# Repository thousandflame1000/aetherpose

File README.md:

# Aetherpose

## Windows：下載、解壓、雙擊啟動

一般使用者請到 [GitHub Releases](https://github.com/thousandflame1000/aetherpose/releases)
下載 `AetherPose-…-windows-x64.zip`，完整解壓後雙擊 **AetherPose.exe**。
不需另裝 Python、Rust 或 SMPL。進入網頁後按「開啟影像骨架」即可使用單鏡頭追蹤。

基本模式使用程式建構的通用人體；IMU 可選配，SMPL 與 GlobalPose 為另行安裝的進階功能。
攝影機不會自動開啟；關閉啟動器會停止本次啟動的服務。
詳細步驟、版本限制與建置方式見 [Windows 快速開始](docs/WINDOWS_QUICKSTART.md)。

母關節融合 v2 已加入影像／IMU 一致性與扭轉歧義保護；量測結果及剩餘限制見 [修正與驗證](docs/parent-fusion-v2.md)。

下方為原始碼／進階功能說明。

使用單鏡頭辨識全身骨架，可搭配 0 顆或多顆 IMU 追蹤器（Arduino Nano 33 BLE）。影像與已校正 IMU 在骨架旋轉空間融合；雙前臂、雙小腿、頭與骨盆六個位置齊備時，自動使用 GlobalPose 的姿態與位移先驗。瀏覽器顯示 SMPL 人體並提供小遊戲與 Combat 對打。

**新版操作與限制：[單鏡頭＋可變數量 IMU](docs/hybrid-runtime.md)。** 舊版 TransPose 程式保留供回歸參考，不再是預設推論來源。

```
IMU 追蹤器 ──BLE──> 後端 aetherpose.exe ──ws :9009──> 網頁控制面板（追蹤器、校正、設定）
                         │
                         └──ws :9009──> frontend/mesh_bridge.py ──ws :9010──> 3D 人體、小遊戲、Combat
                                         (影像／IMU 融合＋GlobalPose)
網頁伺服器：http://127.0.0.1:18080/
```

## 開始使用

本次工作範圍為軟體成熟化，硬體穿戴不列為完成條件。不用 IMU 的環境檢查、模擬展示、驗收與交付步驟見 [軟體展示與驗收](docs/software-delivery.md)。軟體模擬結果保留其來源，不能宣稱真人動作精度。

專案圖文總覽見 [專案整理頁](docs/project-overview.html)。`config.json` 是執行時的本機設定，不納入 Git；首次啟動會建立預設值，也可先複製 `config.example.json` 為 `config.json` 再調整。

```powershell
cd aetherpose
.\setup.ps1      # 安裝主程式套件與編譯後端
.\tools\setup_hybrid.ps1 # 安裝影像模型與隔離的 GlobalPose 環境
.\run.ps1        # 啟動後端、推論與網頁，開啟瀏覽器（已在執行的服務會沿用）
.\run.ps1 -Restart  # 更新程式後：關掉舊服務，後端程式碼較新時重新編譯，再啟動
.\stop.ps1       # 關閉
```

SMPL 模型為選用：未安裝時使用通用人體，已授權模型可在 `external_paths.json` 設定。影像模型與 GlobalPose 由 `tools/setup_hybrid.ps1` 安裝到不進 Git 的 `external/`；只安裝基本影像時可加 `-SkipGlobalPose`。用 `python frontend\external_paths.py` 檢查檔案；加 `--legacy` 可檢查舊 TransPose 資料。完整步驟見 [Hybrid 操作說明](docs/hybrid-runtime.md)。

## 連接埠

18080、9009、9010 只在本機（127.0.0.1）監聽，WebSocket 也只接受本機頁面。9003 與 9002 在所有網路介面上接收 UDP，區域網路上的 Wi-Fi 追蹤器與 Quest 才連得到；同一個網路上的其他裝置也能送資料進來，在不信任的網路上請用 Windows 防火牆擋掉這兩個埠。

| 埠 | 用途 |
|---|---|
| 18080 | 網頁與本機工具 API（`webui/server.py`） |
| 9009 | 後端 WebSocket：追蹤器狀態、設定、指令 |
| 9010 | 推論服務 WebSocket：關節位置與旋轉（頁面據此算出 SMPL 人體網格） |
| 9000（送出） | OSC 骨架輸出，依 VRChat 規格送追蹤器 1–8（髖、胸、雙腳、雙膝、雙肘）與 head；預設 127.0.0.1:9000（VRChat 的 OSC 接收埠），可在「進階 › 系統」分頁修改 |
| 9003（UDP 接收） | Wi-Fi 追蹤器的 UDP 封包；設定在 `config.json` 的 `udp_input_port`，與 OSC 輸出分開 |
| 9002（UDP 接收） | Quest 頭顯與手把的姿態橋接；超過 0.5 秒沒有新資料就不使用，「進階 › 骨架」分頁顯示是否連線 |

## 專案結構

| 位置 | 內容 |
|---|---|
| `src/` | Rust 後端：BLE 接收、姿態融合、IK、OSC 輸出、錄製、WebSocket（埠 9009）。設定存在 `config.json` |
| `src/skeleton/tracker_firmware/` | 追蹤器韌體（x-io Fusion AHRS） |
| `frontend/` | `mesh_bridge.py` 推論服務（埠 9010）、`hybrid_runner.py`、`hybrid_fusion.py`、`vision_pose.py`、`globalpose_worker.py`、`smpl_fk.py`、`external_paths.py`、`body_calibration.py` |
| `webui/` | 瀏覽器介面：主控面板、共用 3D 場景與訓練場（`environment.js`）、小遊戲、Combat、場景物件與道具庫、磁力計校正；`server.py` 頁面伺服器（含本機工具 API）、`run.ps1`／`stop.ps1` |
| `tools/` | `calibrate_tracker.py` 磁力計校正與燒錄、`make_scene_props.py` 產生場景庫的訓練道具、`simulate_trackers.py` 沒有硬體時用 UDP 模擬追蹤器、`imu_axes.py` 不經後端直接用 BLE 檢視單顆 IMU（主介面「進階 › 監控」分頁的「三軸 ↗」開的是同一個頁面） |
| `recordings/` | 「進階 › 系統」分頁錄製的骨架 CSV（不進 git） |
| `logs/` | 後端、推論服務、網頁伺服器的 log 與 BLE 連線紀錄（`run.ps1` 建立，不進 git） |
| `tests/` | 軟體測試；`tests\run_software_checks.ps1` 全部執行，加 `-Live` 會啟動服務測實際流程 |

## 文件

畢設成熟化的核心範圍、分階段工作與實測通過條件見 [畢設執行計畫](docs/graduation-plan.md)。尚未完成的實體測試不得以模擬結果代替。

目前是否達到交付程度與剩餘證據，見 [畢設程度評估](docs/graduation-readiness.md)。真人正／負例的標註及分析流程見 [深蹲試次分析](docs/action-evaluation.md)。

實測前請依 [實驗記錄說明](docs/experiments.md) 保存版本、輸入來源與逐顆追蹤器紀錄。

推論更新偏慢或動作輸入被略過時，依 [效能診斷](docs/performance.md) 保存分段負載與積壓計數。

正式報告的文字工作來源為 [成果報告審閱草稿](docs/thesis-source.md)。它依現行架構與證據重整；實體實驗、作者資料及 Word 排版仍待完成，上層舊計畫書與前三章檔案保留為歷史版本。

提供老師或接手者的原始碼快照，依 [提交包說明](docs/submission.md) 建立與驗證；個人設定、模型及實驗紀錄不會自動納入。

| 文件 | 內容 |
|---|---|
| [HANDOFF.md](HANDOFF.md) | 從零開始：韌體、環境、外部檔案、啟動、磁力計校正、常見問題 |
| [webui/README.md](webui/README.md) | 網頁介面、小遊戲規則、Combat、場景物件、回歸測試 |
| [EXTERNAL_DEPENDENCIES.md](EXTERNAL_DEPENDENCIES.md) | 外部方法、資料與授權 |
| [tools/IMU_AXES_README.md](tools/IMU_AXES_README.md) | 韌體座標軸與單顆 IMU 測試 |
| [docs/acceptance-status.md](docs/acceptance-status.md) | 軟體驗收紀錄 |

## 虛擬 IMU 與遮擋模擬

參見 [互動合成實驗](tools/hybrid_simulation/README.md)：已知 3D 動作、虛擬 IMU、真實 RGB 辨識、遮擋與誤差比較。

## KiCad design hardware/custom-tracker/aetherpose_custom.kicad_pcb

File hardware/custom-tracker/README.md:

# Aetherpose 自製追蹤器 v0.1

2026-10-18。使用者已授權由設計端選型及抓預算，先以 **6 顆**樣品規劃。這是取代 Nano 33 BLE 的新電路，板上整合 MCU／BLE、九軸感測、充電、穩壓與電量量測。

**工程審閱草稿，尚未完成 KiCad 開檔／ERC／DRC、實際焊接、韌體移植及穿戴驗證。不可直接當作可下單的完成品。** `verification.json` 只記錄獨立幾何與連通性檢查，不是 KiCad 認證。未輸出 Gerber，避免未經審核資料被誤送製。

## 選定的第一版

| 功能 | 元件／設計 | 理由與限制 |
|---|---|---|
| MCU、BLE | Espressif ESP32-C3-MINI-1-H4X | 使用原廠 RF 模組，省去裸晶天線調校；取消 Arduino 開發板。首版僅用 BLE，不啟動 Wi-Fi；仍需實測耗電及六顆同連 |
| 加速度、陀螺儀 | Bosch BMI270 | 六軸，移植感測器驅動與 Fusion，不使用 LSM9DS1 的修正倍率 |
| 磁力計 | QST QMC5883P | 保留三軸磁場輸入；採 3×3 mm LGA，避免首版增加更小 WLCSP 的組裝難度。不是 QMC5883L，驅動不可混用 |
| 充電與電源路徑 | TI BQ24075RGTR | 板載充電與負載分流；100 mA USB 輸入限制，約 100 mA 充電設定 |
| 3.3 V | TI TLV75533PDBVR | 500 mA LDO；無升壓電感。低電量可用容量會受 dropout 限制，續航待量測 |
| 電池 | 受保護 1S、4.2 V 滿充、約 250 mAh | 電池須允許至少 110 mA 充電並有 10kΩ 103AT-2 曲線 NTC，或將等效外部 NTC 貼附於電池；不可用 4.35 V 化學體系代換 |
| 充電口 | USB-C，兩個 5.1kΩ CC 下拉 | 僅作 5 V 充電，資料腳未接，沒有 PD／快充 |
| 燒錄 | 六個 UART pogo 焊盤 | 六顆共用 3.3 V USB-UART／治具；沒有每板 USB-UART IC |
| 電源開關 | C&K JS202011CQN DPDT | 同步切換 LDO EN 與電池分壓來源，關機不從 A0 注入電流 |

板框 **45 × 48 mm、雙層、暫定 1.6 mm**；天線向上超出板框約 5.3 mm，因此外殼內部長度至少還要包含突出天線與機構間隙。無穿戴固定孔，採絕緣外殼卡槽固定。此版是功能打樣尺寸，尚未做最小化。

## 開啟與檔案

- `aetherpose_custom.kicad_pro`：最小專案設定，預設線寬 0.2 mm、間距 0.15 mm；需在實際 KiCad 載入時核對規則與板廠能力。
- `aetherpose_custom.kicad_sch`：KiCad 8 原生原理圖，符號內嵌，不依賴外部符號庫。符號採逐腳方塊表達，各接點有網名或 no-connect；所有腳位目前是 passive ERC 類型，所以 ERC 不會替你檢查電源輸出衝突。
- `aetherpose_custom.kicad_pcb`：新板 PCB，精確佈線狀態以 `verification.json` 與板內連線檢視為準；不是先前的 Nano 底板。
- `pcb-preview.svg`／`pcb-preview.png`：從實際路由資料產生的工程預覽，紅色上層、藍色下層。
- `schematic-preview.svg`／`schematic-preview.png`：同一腳位模型的原理圖預覽；不是 KiCad 實際 render，仍須用 KiCad 開檔複核。
- `bom.csv`：44 個板上位置的用量、料號與成本欄。前三個主要 IC 是參考單價，其餘多數為設計預留價，**不是完整已報價的採購單**。
- `pin-netlist.csv`：逐腳網表；`design.json` 是原理圖、PCB 與網表共用來源。
- `COST.md`：成本拆分與小量預算，電池／外殼不混在電子料單價內。
- `FIRMWARE.md`：GPIO、驅動、ADC、BLE 與軸向移植要求；尚未交付可燒錄的自製板韌體。
- `Aetherpose.pretty/`、`fp-lib-table`：隨附 KiCad／Espressif 上游封裝；來源見 `sources/upstream-manifest.json`。

上層 `../bom.csv`、`../aetherpose_carrier.kicad_pcb` 是停用的 Nano 插座底板，請勿採購或混用。

## 電源與充電設計

USB VBUS → BQ24075 IN；BAT → 電池；OUT → VSYS → TLV75533 → 3V3。BQ 的電源路徑可將負載電流與充電分開，避免用一般充電 IC 直接帶負載而影響終止判斷。

第一版 EN1、EN2 固定接地，採 **USB100 模式**。ILIM 以 3.24kΩ 接地，但不使用外部 ILIM 模式，不能按此阻值宣稱輸入 500 mA。ISET 8.87kΩ，按 890 AΩ 典型係數計約 100 mA，元件誤差下可接近 110 mA；輸入限制、負載及溫度可能使實際充電更低。

TMR 懸空保留原廠約 5 小時安全計時；250 mAh 為此設定的初版容量目標。若換成 500 mAh 或更大電池，需重新評估計時設定，不可只替換電池。NTC 開路時應停止充電；首件需用加熱／冷卻與開路測試驗證。無 NTC 的二線電池不可直接插上三線接頭後宣稱已完成溫度監測。

BQ24075 在足夠高的輸入下可將 OUT 調至 5.5 V；本板只允許 **5 V USB（設計輸入上限 5.25 V）**，不能把其 6.6 V 工作額定當作本板輸入額定，TLV75533 的建議輸入上限為 5.5 V。沒有 PD 協商，不可接入自行改線的高壓來源。首版未加入獨立連接器 ESD／浪湧保護元件，需在硬體審閱決定量產保護規格。

SW1：2 是 LDO_EN 公共端，5 是 BAT_SENSE 公共端。2–3／5–6 接通為 ON；2–1／5–4 接通為 OFF。OFF 將 EN 與電池分壓來源接地；充電 IC 仍可為電池充電。開關不是電池總隔離，長期收納仍需拔電池。

R7／R8 是 100kΩ／100kΩ；4.2 V 電池時 BAT_ADC 約 2.1 V。C6 100nF 配合 50kΩ 等效來源，時間常數約 5 ms。ESP32 ADC 需以校準 API 讀電壓，不能使用 Nano 的 `3.3 / 4095` 常數。

## 接頭、燒錄與組裝

J2：**1=BAT+、2=電池 NTC、3=GND**。這是自訂三芯定義，不代表與任意市售三線電池相容；核對極性與 NTC 後才做線束。

TP1=GND、TP2=3V3 參考電壓（僅量測，不注入電源）、TP3=ESP RX、TP4=ESP TX、TP5=BOOT/GPIO9、TP6=CHIP_EN。USB-UART TX 接 TP3、RX 接 TP4，共地；治具先拉 BOOT 低，再以 EN 低→高重設，之後釋放 BOOT 進行 ROM UART 燒錄。正常啟動 BOOT 由 10kΩ 上拉。治具必須使用 3.3 V 邏輯，關機時拔除或三態 UART 訊號。

QMC5883P 需回焊，不以手焊驗證細間距底部焊盤。保留封裝方向與 1 腳標記；現有腳位圖已對照各 IC 資料表，但仍需獨立覆核 **land pattern**。通用 Bosch LGA／QFN 封裝的焊墊、熱焊盤與錫膏設計也須與實際供貨封裝確認，不能只看封裝名稱相似。

天線在板邊外，外殼、電池、線束及金屬不得包住它。磁力計中心設走線／覆銅保留區，量產需按 QST 佈局規則進一步檢查周圍材料與電流迴路。充電器、電池、線束固定後重新做磁力計校正。尚未宣稱與 Nano 同等精度、續航或穩定度。

## 驗證狀態與下一道檢查

已做：資料表腳位與電源設定查閱、以共同網表產生原理圖與 PCB、FreeRouting 單執行緒佈線，以及獨立 named-net 連通性／保守焊墊間距／板邊／保留區檢查（結果以 `verification.json` 為準）。交付草稿關閉了較耗時的 post-route 最佳化；後續以 KiCad 手動調整供電與回流為優先。

本版獨立檢查結果：**PASS，28 個網路、588 段走線、38 個過孔，保守銅間距最小約 0.1507 mm**。這些數字不代表 KiCad DRC 或硬體功能已通過。

仍需：KiCad 實際載入與 ERC／DRC、封裝及機構 1:1 對照、接頭及充電溫度審閱、回焊規格、電源完整性與接地回流審閱。首版走線以 0.2 mm 為主；供電／地線、熱焊盤與接地平面須在 KiCad 內按電流及 RF 要求優化，不能把自動佈線的連通性當成電氣性能驗收。

首件以限流供電檢查 3V3、關機分壓、低電量／USB 插拔、充電電流、NTC、燒錄、感測器 ID 與軸向；移植韌體後才測六顆 BLE、100Hz 目標、延遲及穿戴精度。所有通過項目均應留下實測記錄。

## 重建

`python build_design.py` 會重建原理圖與 **未佈線 placement PCB**，覆蓋先前 PCB；之後必須重新路由或在 KiCad 手動走線。FreeRouting 1.9 使用單執行緒 `-mt 1`；不要使用有已知間距問題的多執行緒最佳化。

目前環境可用 Java 21。`java -jar sources/freerouting-1.9.0.jar -de aetherpose_custom.dsn -do aetherpose_custom.ses -mp 20 -mt 1` 完成後，執行 `python import_and_check.py` 匯入並檢查。此程式需 Shapely。預覽 PNG 需 PyMuPDF，由 SVG 轉換。

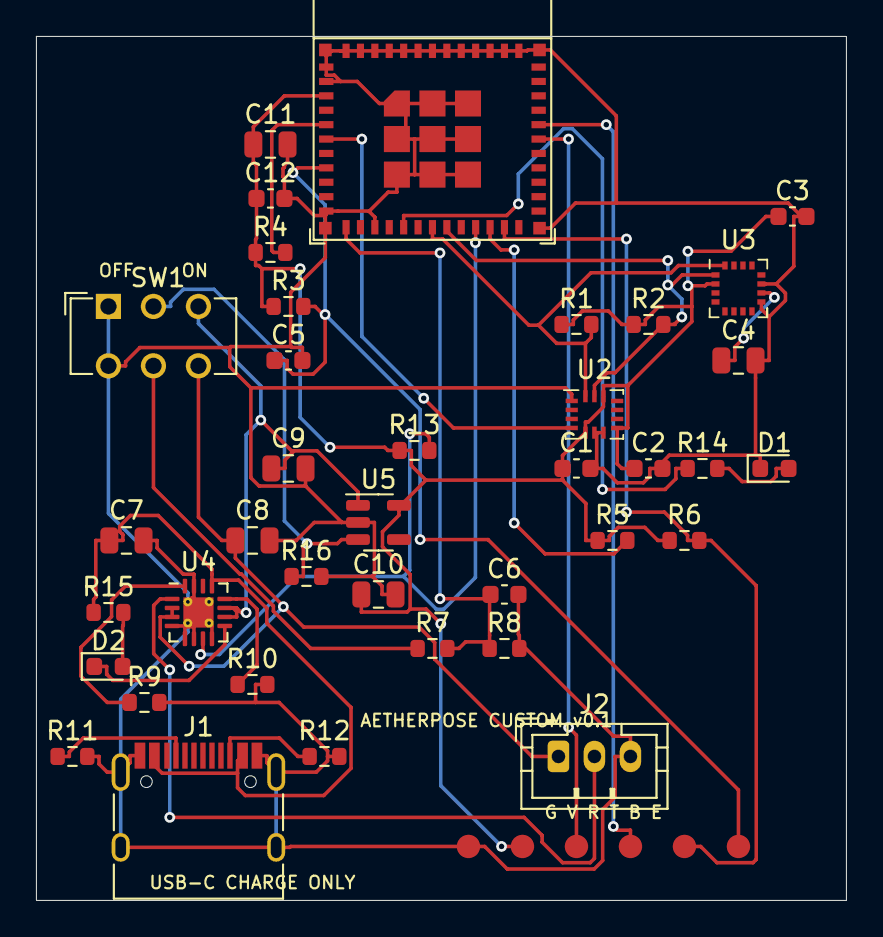
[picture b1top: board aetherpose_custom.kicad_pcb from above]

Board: 2 copper layers, 45.0 x 48.0 mm, 38 parts (0 on the bottom side), 26 nets.

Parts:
C1, C2, C3, C6, C12: 100nF; C_0603_1608Metric
C4: 4.7uF; C_0805_2012Metric
C5: 1uF; C_0603_1608Metric
C7, C8, C9, C10, C11: 10uF_10V_X5R; C_0805_2012Metric
D1: STATUS_GREEN; LED_0603_1608Metric
D2: CHARGE_AMBER; LED_0603_1608Metric
J1: USB-C_CHARGE_ONLY; USB_C_Receptacle_HRO_TYPE-C-31-M-12
J2: BAT+ / NTC / GND; JST_PH_B3B-PH-K_1x03_P2.00mm_Vertical
R1, R2: 4.7k; R_0603_1608Metric
R3, R4, R5, R6, R13: 10k; R_0603_1608Metric
R7, R8: 100k; R_0603_1608Metric
R9: 8.87k_1pct; R_0603_1608Metric
R10: 3.24k_1pct; R_0603_1608Metric
R11, R12: 5.1k_1pct; R_0603_1608Metric
R14, R15: 2.2k; R_0603_1608Metric
R16: 1M; R_0603_1608Metric
SW1: JS202011CQN_DPDT; SW_CuK_JS202011CQN_DPDT_Straight
U1: ESP32-C3-MINI-1-H4X; ESP32-C3-MINI-1
U2: BMI270; Bosch_LGA-14_3x2.5mm_P0.5mm
U3: QMC5883P; LGA-16_3x3mm_P0.5mm
U4: BQ24075RGTR; VQFN-16-1EP_3x3mm_P0.5mm_EP1.68x1.68mm_ThermalVias
U5: TLV75533PDBVR; SOT-23-5

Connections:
+3V3: C1.1, C2.1, C3.1, C10.1, C11.1, C12.1, R1.1, R2.1, R3.1, R4.1, R5.1, R6.1, R13.1, U1.3, U2.5, U2.8, U2.12, U3.2, U5.5
BAT_ADC: C6.1, R7.2, R8.1, U1.12
BAT_NTC: J2.2, U4.1
BAT_SENSE: R7.1, SW1.5
BOOT: R6.2, U1.23
CC1: J1.A5, R11.1
CC2: J1.B5, R12.1
CHG: D2.1, U4.9
CHG_ILIM: R10.1, U4.12
CHG_ISET: R9.1, U4.16
CHG_LED_A: D2.2, R15.2
CHIP_EN: C5.1, R3.2, U1.8
GND: C1.2, C2.2, C3.2, C4.2, C5.2, C6.2, C7.2, C8.2, C9.2, C10.2, C11.2, C12.2, D1.1, J1.A1, J1.A12, J1.B1, J1.B12, J1.S1, J2.3, R8.2, R9.2, R10.2, R11.2, R12.2, R16.2, SW1.1, SW1.4, U1.1, U1.2, U1.11, U1.14, U1.36, U1.37, U1.38, U1.39, U1.40, U1.41, U1.42, U1.43, U1.44, U1.45, U1.46, U1.47, U1.48, U1.49, U1.50, U1.51, U1.52, U1.53, U2.1, U2.6, U2.7, U3.9, U3.11, U4.4, U4.5, U4.6, U4.8, U4.15, U4.17, U5.2
I2C_SCL: R2.2, U1.19, U2.13, U3.1
I2C_SDA: R1.2, U1.18, U2.14, U3.16
IMU_INT: U1.6, U2.4
LDO_EN: R16.1, SW1.2, U5.3
LED_A: D1.2, R14.2
LED_DRV: R14.1, U1.16
MAG_CAP: C4.1, U3.10
PGOOD: R13.2, U1.21, U4.7
STRAP2: R4.2, U1.5
STRAP8: R5.2, U1.22
VBAT: C8.1, J2.1, SW1.6, U4.2, U4.3
VBUS: C7.1, J1.A4, J1.A9, J1.B4, J1.B9, R15.1, U4.13
VSYS: C9.1, SW1.3, U4.10, U4.11, U5.1

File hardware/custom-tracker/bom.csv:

Reference,Value_MPN,Footprint,Qty_per_board,Qty_for_6,USD_budget_each,Price_status,Source
U1,ESP32-C3-MINI-1-H4X,Aetherpose:ESP32-C3-MINI-1,1,6,4.01,reference_1pc,https://www.mouser.com/en/ProductDetail/Espressif-Systems/ES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
U2,BMI270,Aetherpose:Bosch_LGA-14_3x2.5mm_P0.5mm,1,6,1.8389,reference_1pc,https://www.lcsc.com/product-detail/C2836813.html
U3,QMC5883P,Aetherpose:LGA-16_3x3mm_P0.5mm,1,6,1.5551,reference_1pc,https://www.lcsc.com/product-detail/C2847467.html
U4,BQ24075RGTR,Aetherpose:VQFN-16-1EP_3x3mm_P0.5mm_EP1.68x1.68mm_ThermalVias,1,6,1.2,engineering_allowance_not_quote,https://www.lcsc.com/product-detail/C15464.html
U5,TLV75533PDBVR,Aetherpose:SOT-23-5,1,6,0.3,engineering_allowance_not_quote,https://www.ti.com/product/TLV755P/part-details/TLV75533PDBVR
J1,USB-C_CHARGE_ONLY,Aetherpose:USB_C_Receptacle_HRO_TYPE-C-31-M-12,1,6,0.4,engineering_allowance_not_quote,
J2,BAT+ / NTC / GND,Aetherpose:JST_PH_B3B-PH-K_1x03_P2.00mm_Vertical,1,6,0.3,engineering_allowance_not_quote,
SW1,JS202011CQN_DPDT,Aetherpose:SW_CuK_JS202011CQN_DPDT_Straight,1,6,0.8,engineering_allowance_not_quote,
R1,4.7k,Aetherpose:R_0603_1608Metric,1,6,0.008,engineering_allowance_not_quote,
R2,4.7k,Aetherpose:R_0603_1608Metric,1,6,0.008,engineering_allowance_not_quote,
R3,10k,Aetherpose:R_0603_1608Metric,1,6,0.008,engineering_allowance_not_quote,
R4,10k,Aetherpose:R_0603_1608Metric,1,6,0.008,engineering_allowance_not_quote,
R5,10k,Aetherpose:R_0603_1608Metric,1,6,0.008,engineering_allowance_not_quote,
R6,10k,Aetherpose:R_0603_1608Metric,1,6,0.008,engineering_allowance_not_quote,
R7,100k,Aetherpose:R_0603_1608Metric,1,6,0.008,engineering_allowance_not_quote,
R8,100k,Aetherpose:R_0603_1608Metric,1,6,0.008,engineering_allowance_not_quote,
R9,8.87k_1pct,Aetherpose:R_0603_1608Metric,1,6,0.008,engineering_allowance_not_quote,
R10,3.24k_1pct,Aetherpose:R_0603_1608Metric,1,6,0.008,engineering_allowance_not_quote,
R11,5.1k_1pct,Aetherpose:R_0603_1608Metric,1,6,0.008,engineering_allowance_not_quote,
R12,5.1k_1pct,Aetherpose:R_0603_1608Metric,1,6,0.008,engineering_allowance_not_quote,
R13,10k,Aetherpose:R_0603_1608Metric,1,6,0.008,engineering_allowance_not_quote,
R14,2.2k,Aetherpose:R_0603_1608Metric,1,6,0.008,engineering_allowance_not_quote,
R15,2.2k,Aetherpose:R_0603_1608Metric,1,6,0.008,engineering_allowance_not_quote,
R16,1M,Aetherpose:R_0603_1608Metric,1,6,0.008,engineering_allowance_not_quote,
C1,100nF,Aetherpose:C_0603_1608Metric,1,6,0.015,engineering_allowance_not_quote,
C2,100nF,Aetherpose:C_0603_1608Metric,1,6,0.015,engineering_allowance_not_quote,
C3,100nF,Aetherpose:C_0603_1608Metric,1,6,0.015,engineering_allowance_not_quote,
C4,4.7uF,Aetherpose:C_0805_2012Metric,1,6,0.03,engineering_allowance_not_quote,
C5,1uF,Aetherpose:C_0603_1608Metric,1,6,0.015,engineering_allowance_not_quote,
C6,100nF,Aetherpose:C_0603_1608Metric,1,6,0.015,engineering_allowance_not_quote,
C7,10uF_10V_X5R,Aetherpose:C_0805_2012Metric,1,6,0.04,engineering_allowance_not_quote,
C8,10uF_10V_X5R,Aetherpose:C_0805_2012Metric,1,6,0.04,engineering_allowance_not_quote,
C9,10uF_10V_X5R,Aetherpose:C_0805_2012Metric,1,6,0.04,engineering_allowance_not_quote,
C10,10uF_10V_X5R,Aetherpose:C_0805_2012Metric,1,6,0.04,engineering_allowance_not_quote,
C11,10uF_10V_X5R,Aetherpose:C_0805_2012Metric,1,6,0.04,engineering_allowance_not_quote,
C12,100nF,Aetherpose:C_0603_1608Metric,1,6,0.015,engineering_allowance_not_quote,
D1,STATUS_GREEN,Aetherpose:LED_0603_1608Metric,1,6,0.03,engineering_allowance_not_quote,
D2,CHARGE_AMBER,Aetherpose:LED_0603_1608Metric,1,6,0.03,engineering_allowance_not_quote,
TP1,GND,Aetherpose:TestPad_1.3mm,1,6,0,engineering_allowance_not_quote,
TP2,+3V3,Aetherpose:TestPad_1.3mm,1,6,0,engineering_allowance_not_quote,
TP3,UART_RX,Aetherpose:TestPad_1.3mm,1,6,0,engineering_allowance_not_quote,
TP4,UART_TX,Aetherpose:TestPad_1.3mm,1,6,0,engineering_allowance_not_quote,
TP5,BOOT,Aetherpose:TestPad_1.3mm,1,6,0,engineering_allowance_not_quote,
TP6,CHIP_EN,Aetherpose:TestPad_1.3mm,1,6,0,engineering_allowance_not_quote,

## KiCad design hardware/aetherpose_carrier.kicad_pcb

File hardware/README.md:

# Aetherpose 可穿戴追蹤器底板 v0.1

> **2026-10-18 方案停用：使用者已明確要求降低成本、以自製追蹤器取代 Nano 33 BLE。** 本目錄既有 `aetherpose_carrier.kicad_pcb`、`bom.csv` 與預覽僅為舊底板草稿，不是新板設計或採購清單。新方向見 [自製追蹤器設計需求](custom-tracker/DESIGN.md)。

2026-10-18。已選方向：沿用 **Arduino Nano 33 BLE 原版 ABX00030／帶針 ABX00034（LSM9DS1）**，製作供電與固定底板；六個穿戴位置各用一套。

這是已佈線的 PCB 工程草稿。尚未經 KiCad 開檔／DRC、實物配合及打樣驗證，**不是已驗收的量產或直接下單資料**。沒有產生 Gerber，以免將未通過正式檢查的資料誤送製。

## 檔案

- `aetherpose_carrier.kicad_pcb`：KiCad 8 格式，內嵌自訂焊盤，60 × 50 mm、雙層、1.6 mm；無需外部封裝庫即可檢視 PCB。沒有附原理圖同步工程。
- `pcb-preview.svg`：頂視圖，紅色頂層、藍色底層；虛線為 Nano 暫定外形。
- `build_carrier.py`：產生 PCB 與預覽的來源。
- `layout.json`、`check_layout.py`、`verification.txt`：幾何及連通性檢查資料與結果；不能取代 KiCad DRC。
- `bom.csv`：每套與六套用量；外接模組、開關、電池亦列出。

## 已對照專案的功能

來源：`../README.md`、`../HANDOFF.md`、`../src/skeleton/tracker_firmware/tracker_firmware.ino`。

追蹤器供六個部位（頭、胸、左右前臂、左右小腿）使用。現行韌體透過 ArduinoBLE 傳送方向、加速度、陀螺儀、磁力計及電量，傳送間隔 10 ms，IMU 設定 119 Hz。3D、TransPose、遊戲、Combat 由電腦執行，底板不需增加處理器。

不把 Nano 33 BLE Rev2 或 Sense Rev2 視為免改韌體替代品；其感測器必須另行核對。追蹤器 ID 仍由 MAC 末位推得，六顆組裝後要確認 ID 沒有碰撞；末位不是唯一性保證。

## 電路連線（本文件為接線依據）

```text
受保護 1S LiPo ──> 外接充電／升壓模組 BAT（電池插座）
模組 USB         <── 充電線
模組 5V 輸出     ──> J1.1 ── J2.1 ──[SW1 第一極]── J2.2 ──> Nano VIN
模組 BAT 量測點  ──> J1.2 ── J2.3 ──[SW1 第二極]── J2.4 ──> R1 100k ──┬──> Nano A0
模組 GND         ──> J1.3 ──> Nano GND / R2 / C1                      │
                                                                      R2 100k
                                                                      │
                                                                     GND
Nano A0 ── C1 100nF ── GND
```

SW1 是外接 **DPST ON/OFF 雙極同步開關**，接通時 J2.1–2 與 J2.3–4 同時閉合；四條線連到 J2。也可用 DPDT ON/ON 開關，每極只接公共端與同一方向的接點，另一方向懸空作 OFF。不可把 J2.2–3 當一對短接。底板沒有內建充電晶片、USB 充電插座或升壓晶片。

J1 使用三芯線接外部模組的 **5V、BAT、GND**，不是把模組整排直接插到 J1。BAT 必須是電池實際電壓，不是 VS 或 5V。J1.2 不承擔負載供電。

100k / 100k 對應現行韌體設定。電池 4.2 V 時 A0 理論為 2.1 V，分壓電流 21 µA；C1 用於 ADC 濾波，等效 RC 時間常數 5 ms。電量為電壓線性估算，非精確剩餘容量。關機時雙極開關隔離 BAT，避免透過 A0 對未供電 Nano 注入電流。

## 外接電源模組與電池

可用 Adafruit PowerBoost 1000C 作參考：5V 升壓輸出接 J1.1、BAT 接 J1.2、GND 接 J1.3；電池接模組本身電池插座。其預設 1 A 充電，電池必須明確允許至少 1 A 充電，並具適當保護；初版可採容量約 2000 mAh 且資料表符合充放電規格的 1S 電池。不可直接替換成未核對充電電流的小容量穿戴電池。此模組未設計直接安裝封裝，放在外殼獨立隔艙，以線束連接；不是一片 PCB 全部整合。

若改用較小模組，先核對 5 V 穩壓輸出、電池保護、充電電流及實際接線。不要使用單純充電板直接供 VIN。供電走 VIN，不接 Nano 3V3 或 VUSB，不需切 Nano 焊橋。Nano 3.3 V I/O 不耐 5 V。

燒錄前關閉 SW1，再接 Nano USB；充電接電源模組 USB。開關只關追蹤器負載，不是電池總隔離開關；模組仍可能有待機耗電，長期收納需斷電池。初次充電及熱測在桌面進行。

## 機構與佈局

U1 使用兩條 1×15、2.54 mm 母座，排距 15.24 mm。PCB 自訂 U1 焊盤號遵照 ABX00030 資料表：1=D13、4=A0、14=GND、15=VIN；16=TX、19=GND、30=D12。**與常見 Nano 封裝編號不同，不可直接替換封裝！** 頂視 USB 朝左，VIN 在下排最左，D13 在下排最右。焊接前以實物絲印及官方 pinout 再核對。

四個 Ø3.2 mm 非金屬化固定孔位於 (4,4)、(56,4)、(4,46)、(56,46) mm。採尼龍螺絲與絕緣外殼，底板不直接接觸皮膚。尺寸尚未依使用者既有外殼核對。

右側 (43,14)–(55,25) mm 設上下層禁止走線／覆銅區，作暫定天線保留；不是廠商保證的 RF keepout。需依實際 Nano／NINA 模組天線位置擴大核對，電池、線束、金屬與人體遮蔽也要實測。電源模組與電池避開 IMU 及天線，不疊在感測器上，線束固定後重新做磁力計校正。

## 製板前與首件驗證

1. 用 KiCad 8 或更新版開啟 PCB，核對檔案解析、封裝、焊盤號、孔徑與 Nano 插座方向；按實物列印 1:1 紙樣。
2. 建立原理圖並與上述連線逐一對照；原理圖轉 PCB 時須保留這個自訂 U1 編號。補齊未使用接點的 no-connect 意圖。
3. 跑 KiCad DRC，處理所有短路、未連線、間距、孔邊與絲印問題；確認板廠規則後輸出 Gerber／鑽孔並用 Gerber viewer 複核。
4. 未插 Nano、未接電池時，量測電源無短路、開關兩極隔離、分壓值與接頭極性。用限流電源驗證模組與底板。
5. 插 Nano 後量測 VIN 約 5–5.2 V、A0 不超過 3.3 V；4.2 V 電池時 A0 約 2.1 V。驗證 OFF 時 VIN 及 A0 已放電、USB 燒錄、充電溫升及續航。
6. 六顆逐一確認 ID、BLE 封包、電量、三軸方向與磁校正，再同時穿戴驗證斷線率與實際更新率。沒有實測前不宣稱達到 100 Hz 或任何續航數字。

## 官方參考

- Arduino Nano 33 BLE：https://docs.arduino.cc/hardware/nano-33-ble/
- ABX00030 pinout：https://docs.arduino.cc/resources/pinouts/ABX00030-full-pinout.pdf
- ABX00030 datasheet：https://docs.arduino.cc/resources/datasheets/ABX00030-datasheet.pdf
- PowerBoost 1000C：https://learn.adafruit.com/adafruit-powerboost-1000c-load-share-usb-charge-boost

重建：在本目錄執行 `python build_carrier.py`，再執行 `python check_layout.py`。

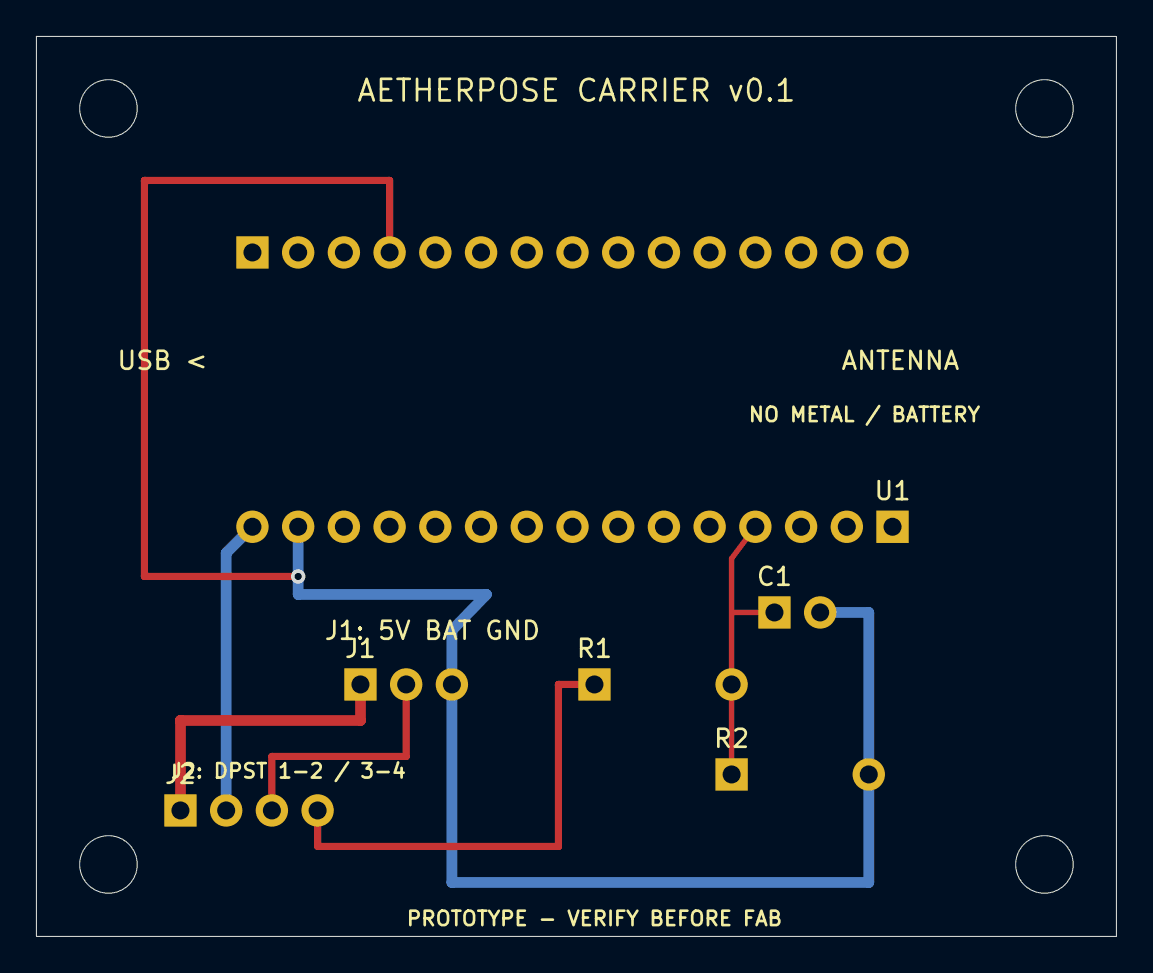
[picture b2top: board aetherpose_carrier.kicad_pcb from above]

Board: 2 copper layers, 60.0 x 50.0 mm, 6 parts (0 on the bottom side), 6 nets.

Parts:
C1: 100nF_2.54mm; C1
J1: 1:5V 2:BAT 3:GND; J1
J2: DPST_SWITCH:1-2,3-4; J2
R1: 100k_1pct_DIN0207; R1
R2: 100k_1pct_DIN0207; R2
U1: Nano_33_BLE_ABX00030_USB_LEFT; U1

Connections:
+5V_IN: J1.1, J2.1
BAT_ADC: C1.1, R1.2, R2.1, U1.4
GND: C1.2, J1.3, R2.2, U1.14, U1.19
VBAT_IN: J1.2, J2.3
VBAT_SW: J2.4, R1.1
VIN_SW: J2.2, U1.15

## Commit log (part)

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2026-03-06 UI: convert toolbar buttons to icons, compact theme, sidebar resize persistence
